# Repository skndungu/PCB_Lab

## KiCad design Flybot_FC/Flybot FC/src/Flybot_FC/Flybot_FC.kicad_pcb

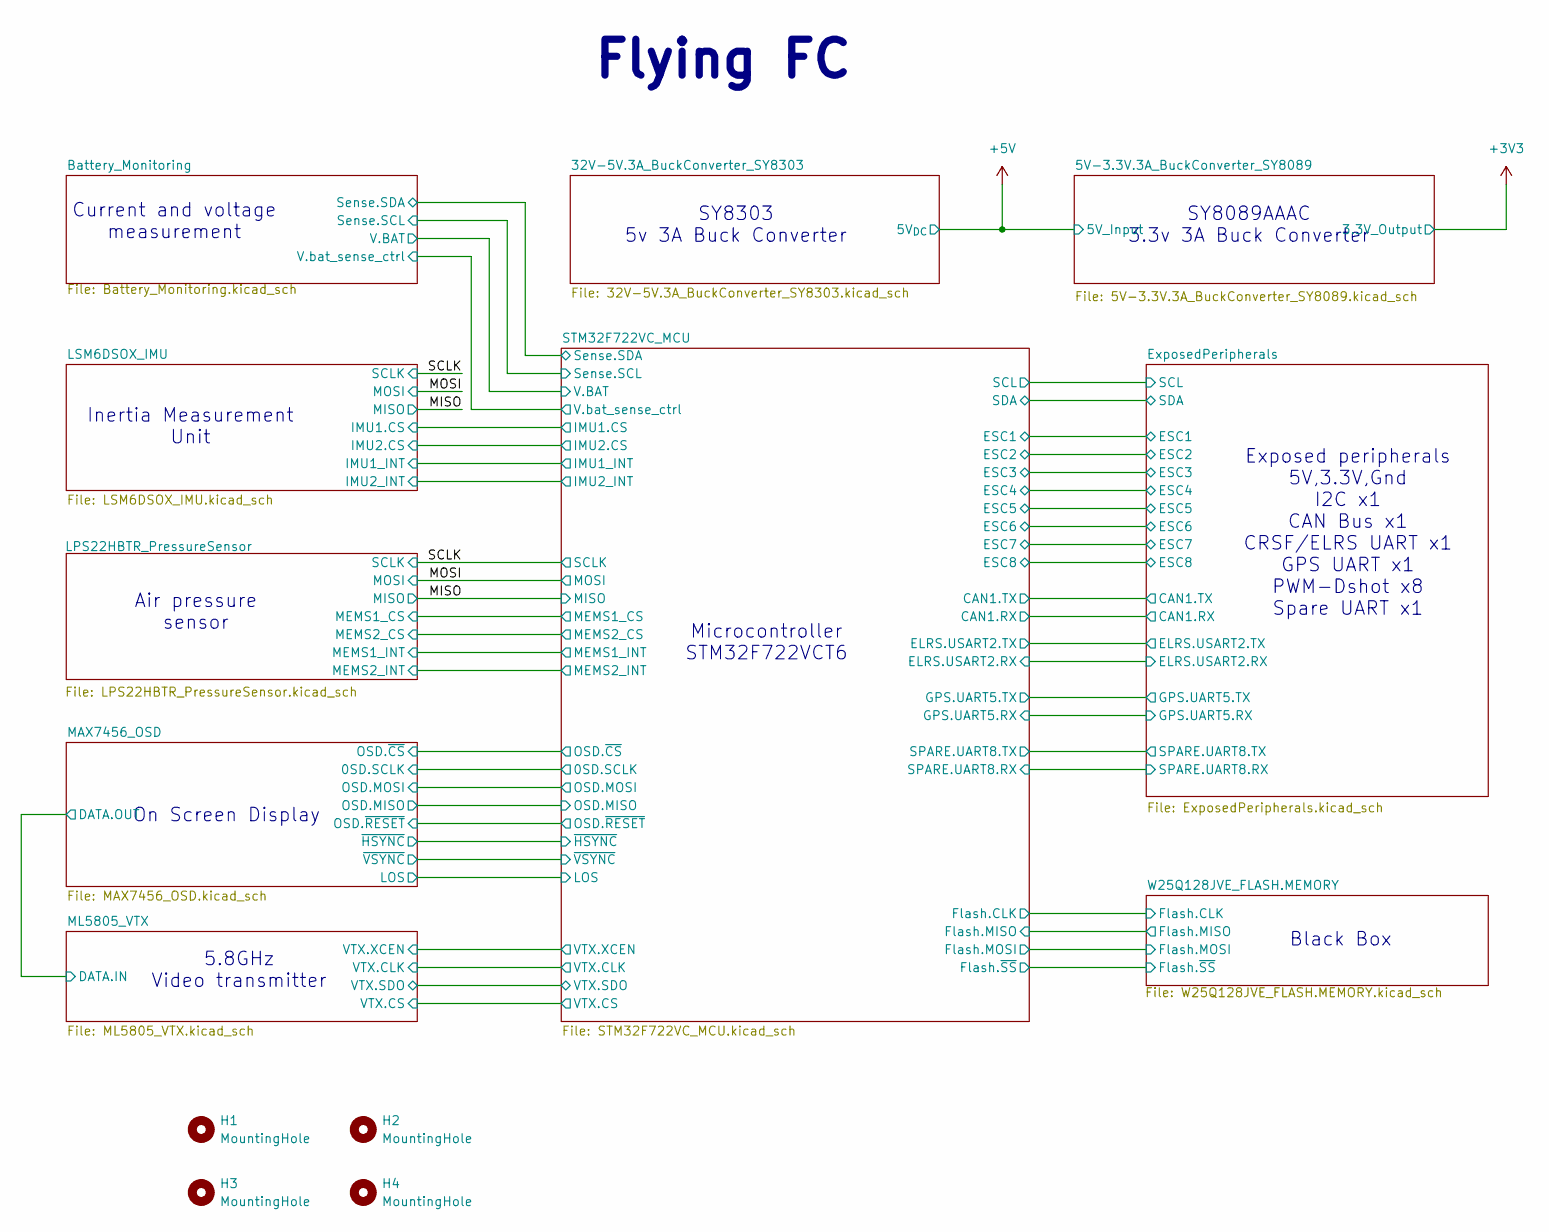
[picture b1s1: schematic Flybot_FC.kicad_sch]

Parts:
H1, H2, H3, H4: MountingHole; MountingHole_3mm

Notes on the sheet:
Inertia Measurement Unit
Microcontroller STM32F722VCT6
5.8GHz Video transmitter
Air pressure sensor
Flying FC
On Screen Display
SY8303 5v 3A Buck Converter
Exposed peripherals 5V,3.3V,Gnd I2C x1 CAN Bus x1 CRSF/ELRS UART x1 GPS UART x1 PWM-Dshot x8 Spare UART x1
SY8089AAAC 3.3v 3A Buck Converter
Black Box
Current and voltage measurement

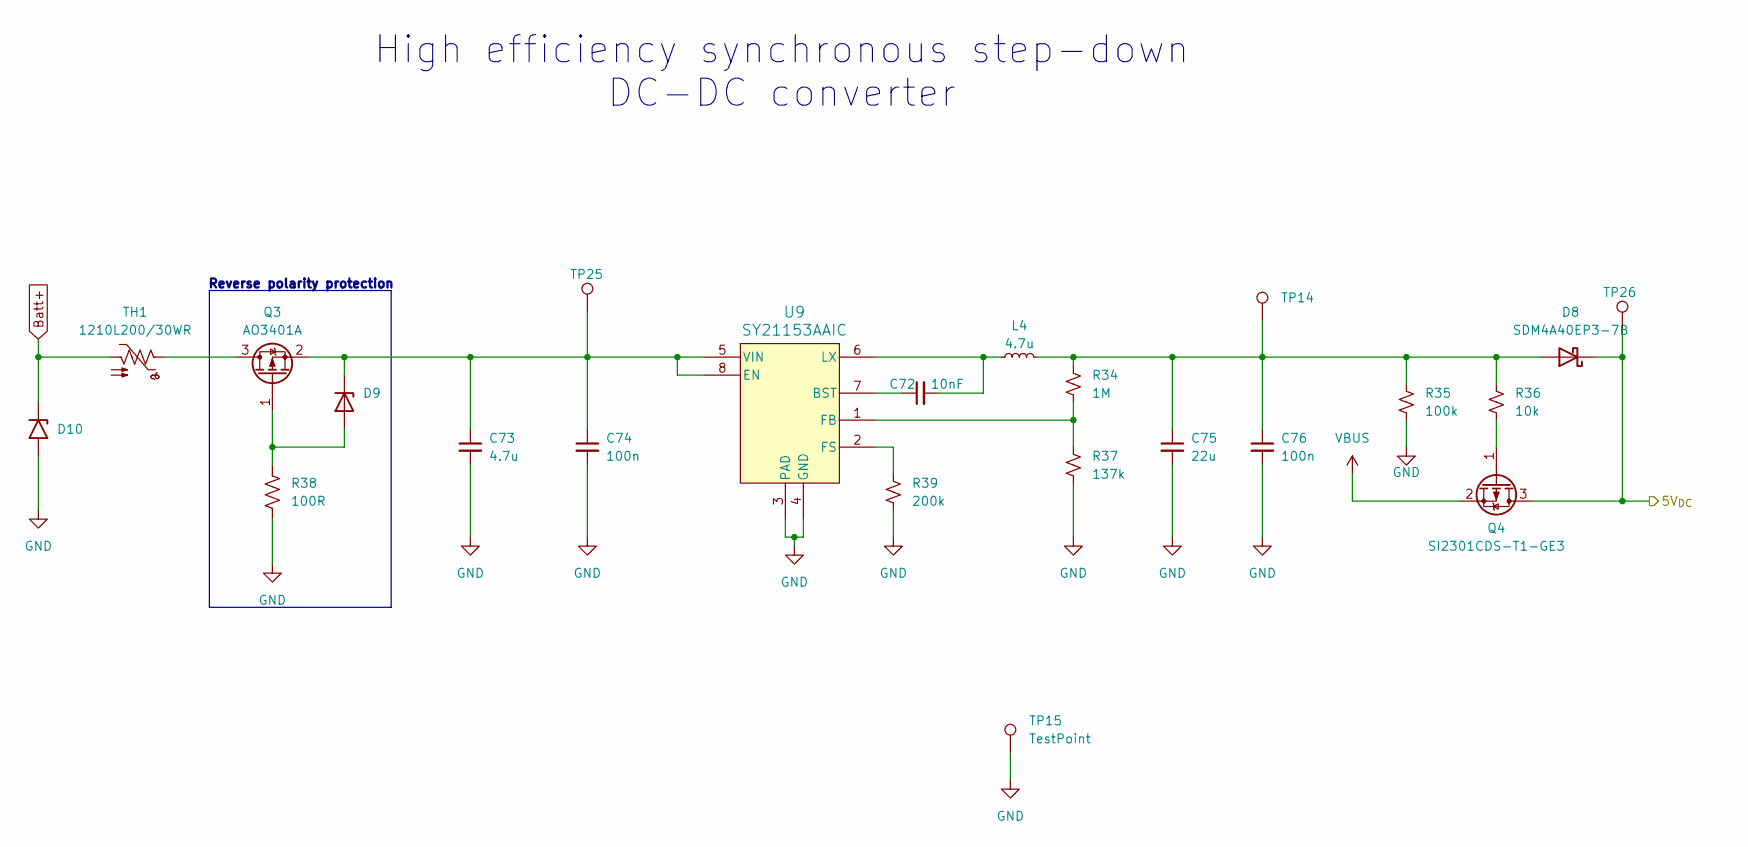
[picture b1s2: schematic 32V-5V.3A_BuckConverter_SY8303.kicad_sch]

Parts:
C72: 10nF; C_0402_1005Metric; JLC# C14663
C73: 4.7u; C_0603_1608Metric; JLC# C19702
C74: 100n; C_0402_1005Metric; JLC# C14663
C75: 22u; C_0402_1005Metric; JLC# C59461
C76: 100n; C_0402_1005Metric; JLC# C59461
D8: SDM4A40EP3-7B; D_0603_1608Metric
D9: BZX884B30L-G3-08; D_0402_1005Metric
D10: D15V0S1U2LP1610-7; D_0603_1608Metric
L4: 4.7u; L_1210_3225Metric; JLC# AFE322520S4R7MBT
Q3: AO3401A; SOT-23
Q4: SI2301CDS-T1-GE3; SOT-23
R34: 1M; R_0402_1005Metric; JLC# C23074
R35: 100k; R_0402_1005Metric; JLC# C25804
R36: 10k; R_0402_1005Metric; JLC# C25804
R37: 137k; R_0402_1005Metric; JLC# C25804
R38: 100R; R_0402_1005Metric
R39: 200k; R_0402_1005Metric; JLC# C2960716
TH1: 1210L200/30WR; Fuse_1206_3216Metric
TP14, TP15, TP25, TP26: TestPoint; TestPoint_Pad_D1.0mm
U9: SY21153AAIC; TSOT-23-8; JLC# C2071517

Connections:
+5V: D8.1 (K), Q4.3 (D), TP26.1; also elsewhere on the board
Batt+: D10.1 (A1), TH1.2; also elsewhere on the board
GND: C73.2, C74.2, C75.2, C76.2, D10.2 (A2), R35.2, R37.2, R38.2, R39.2, TP15.1, U9.3 (PAD), U9.4 (GND); also elsewhere on the board
unnamed: C75.1, C76.1, D8.2 (A), L4.2, R34.1, R35.1, R36.1, TP14.1
unnamed: D9.2 (A), Q3.1 (G), R38.1
unnamed: C73.1, C74.1, D9.1 (K), Q3.2 (S), TP25.1, U9.5 (VIN), U9.8 (EN)
unnamed: Q3.3 (D), TH1.1
unnamed: Q4.1 (G), R36.2
unnamed: C72.1, U9.7 (BST)
unnamed: R34.2, R37.1, U9.1 (FB)
unnamed: R39.1, U9.2 (FS)
unnamed: C72.2, L4.1, U9.6 (LX)
VBUS: Q4.2 (S); also elsewhere on the board

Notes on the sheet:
High efficiency synchronous step-down DC-DC converter
Reverse polarity protection

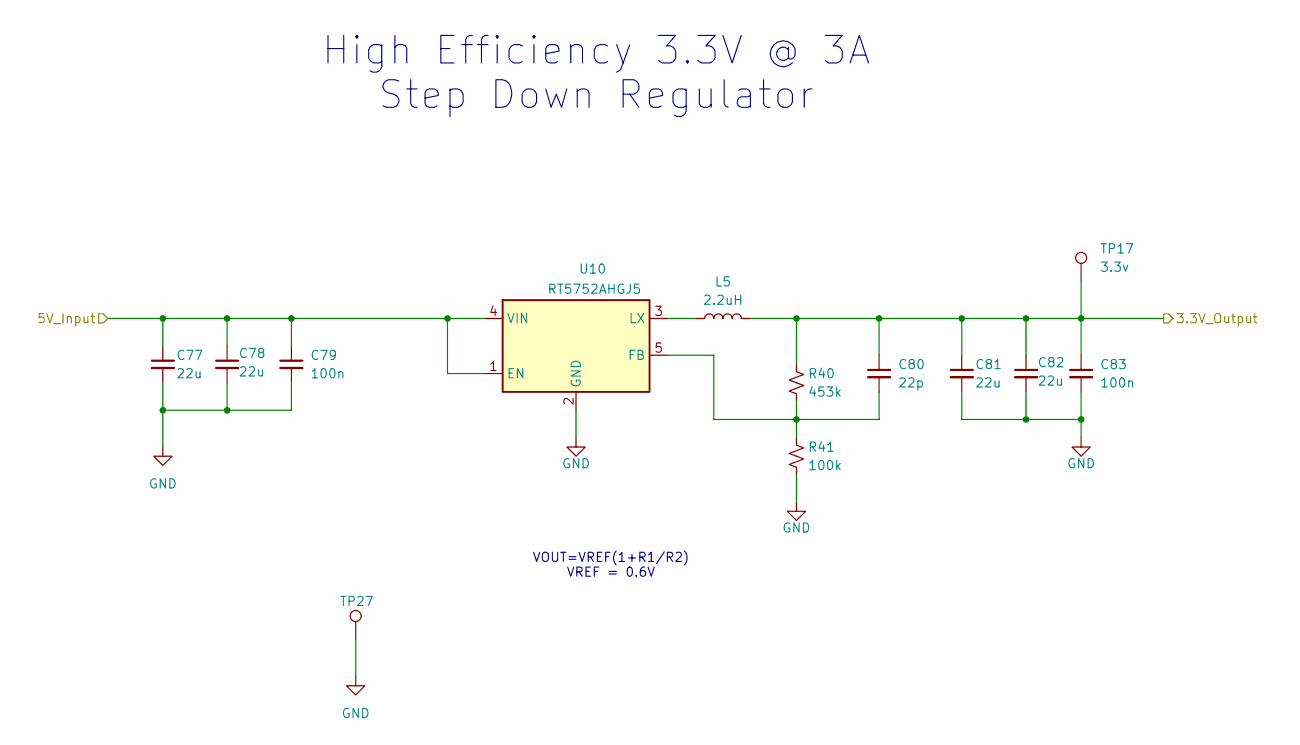
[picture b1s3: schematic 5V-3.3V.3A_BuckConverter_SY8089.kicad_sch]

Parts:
C77, C78, C81, C82: 22u; C_0402_1005Metric
C79, C83: 100n; C_0402_1005Metric
C80: 22p; C_0402_1005Metric
L5: 2.2uH; L_Murata_DFE201610P; MPN APH201610C2R2MP01
R40: 453k; R_0402_1005Metric
R41: 100k; R_0402_1005Metric
TP17: 3.3v; TestPoint_Pad_D1.0mm
TP27: TestPoint; TestPoint_Pad_D1.0mm
U10: RT5752AHGJ5; SOT-23-5

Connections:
+3V3: C80.1, C81.1, C82.1, C83.1, L5.2, R40.1, TP17.1; also elsewhere on the board
+5V: C77.1, C78.1, C79.1, U10.1 (EN), U10.4 (VIN); also elsewhere on the board
GND: C77.2, C78.2, C79.2, C81.2, C82.2, C83.2, R41.2, TP27.1, U10.2 (GND); also elsewhere on the board
unnamed: C80.2, R40.2, R41.1, U10.5 (FB)
unnamed: L5.1, U10.3 (LX)

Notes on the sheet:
VOUT=VREF(1+R1/R2) VREF = 0.6V
High Efficiency 3.3V @ 3A Step Down Regulator

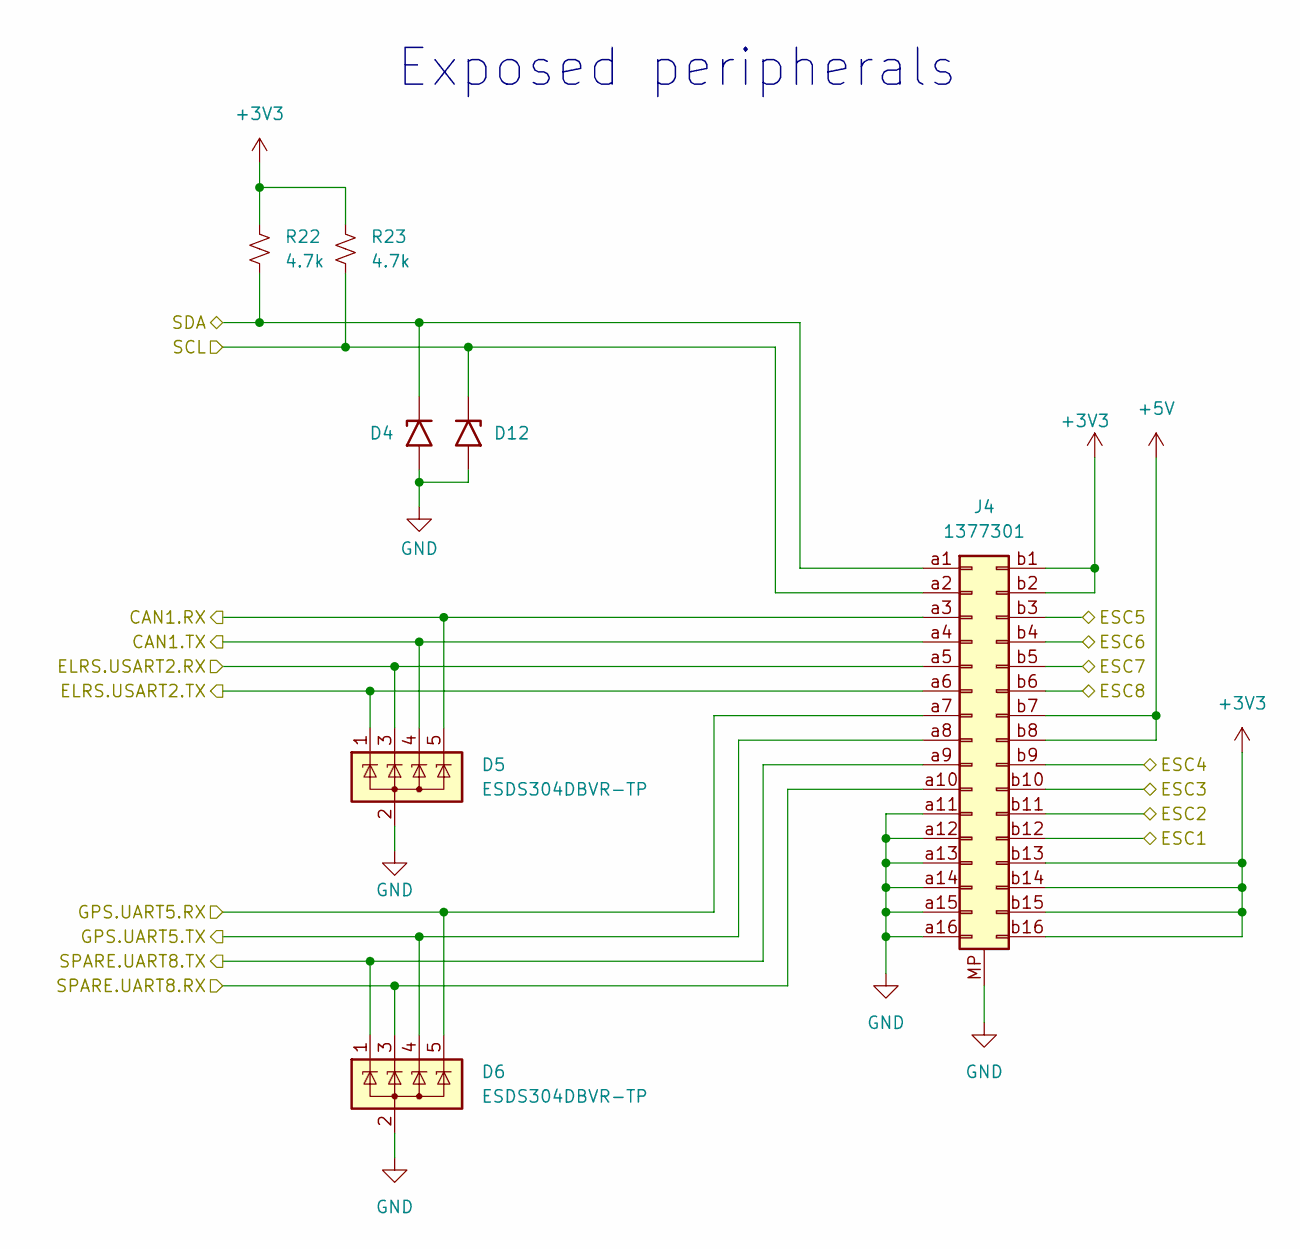
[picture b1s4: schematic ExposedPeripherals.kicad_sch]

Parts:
D4, D12: D1213A-01LP4-7B; D_0402_1005Metric
D5, D6: ESDS304DBVR-TP; SOT-23-5
J4: 1377301; PHOENIX_1377301
R22, R23: 4.7k; R_0402_1005Metric

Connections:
+3V3: J4.b1, J4.b2, J4.b13, J4.b14, J4.b15, J4.b16, R22.1, R23.1; also elsewhere on the board
+5V: J4.b7, J4.b8; also elsewhere on the board
/ExposedPeripherals/CAN1.RX: D5.5 (K), J4.a3; also elsewhere on the board
/ExposedPeripherals/CAN1.TX: D5.4 (K), J4.a4; also elsewhere on the board
/ExposedPeripherals/ELRS.USART2.RX: D5.3 (K), J4.a5; also elsewhere on the board
/ExposedPeripherals/ELRS.USART2.TX: D5.1 (K), J4.a6; also elsewhere on the board
/ExposedPeripherals/ESC1: J4.b12; also elsewhere on the board
/ExposedPeripherals/ESC2: J4.b11; also elsewhere on the board
/ExposedPeripherals/ESC3: J4.b10; also elsewhere on the board
/ExposedPeripherals/ESC4: J4.b9; also elsewhere on the board
/ExposedPeripherals/ESC5: J4.b3; also elsewhere on the board
/ExposedPeripherals/ESC6: J4.b4; also elsewhere on the board
/ExposedPeripherals/ESC7: J4.b5; also elsewhere on the board
/ExposedPeripherals/ESC8: J4.b6; also elsewhere on the board
/ExposedPeripherals/GPS.UART5.RX: D6.5 (K), J4.a7; also elsewhere on the board
/ExposedPeripherals/GPS.UART5.TX: D6.4 (K), J4.a8; also elsewhere on the board
/ExposedPeripherals/SCL: D12.1 (A1), J4.a2, R23.2; also elsewhere on the board
/ExposedPeripherals/SDA: D4.1 (A1), J4.a1, R22.2; also elsewhere on the board
/ExposedPeripherals/SPARE.UART8.RX: D6.3 (K), J4.a10; also elsewhere on the board
/ExposedPeripherals/SPARE.UART8.TX: D6.1 (K), J4.a9; also elsewhere on the board
GND: D4.2 (A2), D5.2 (A), D6.2 (A), D12.2 (A2), J4.MP, J4.a11, J4.a12, J4.a13, J4.a14, J4.a15, J4.a16; also elsewhere on the board

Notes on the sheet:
Exposed peripherals

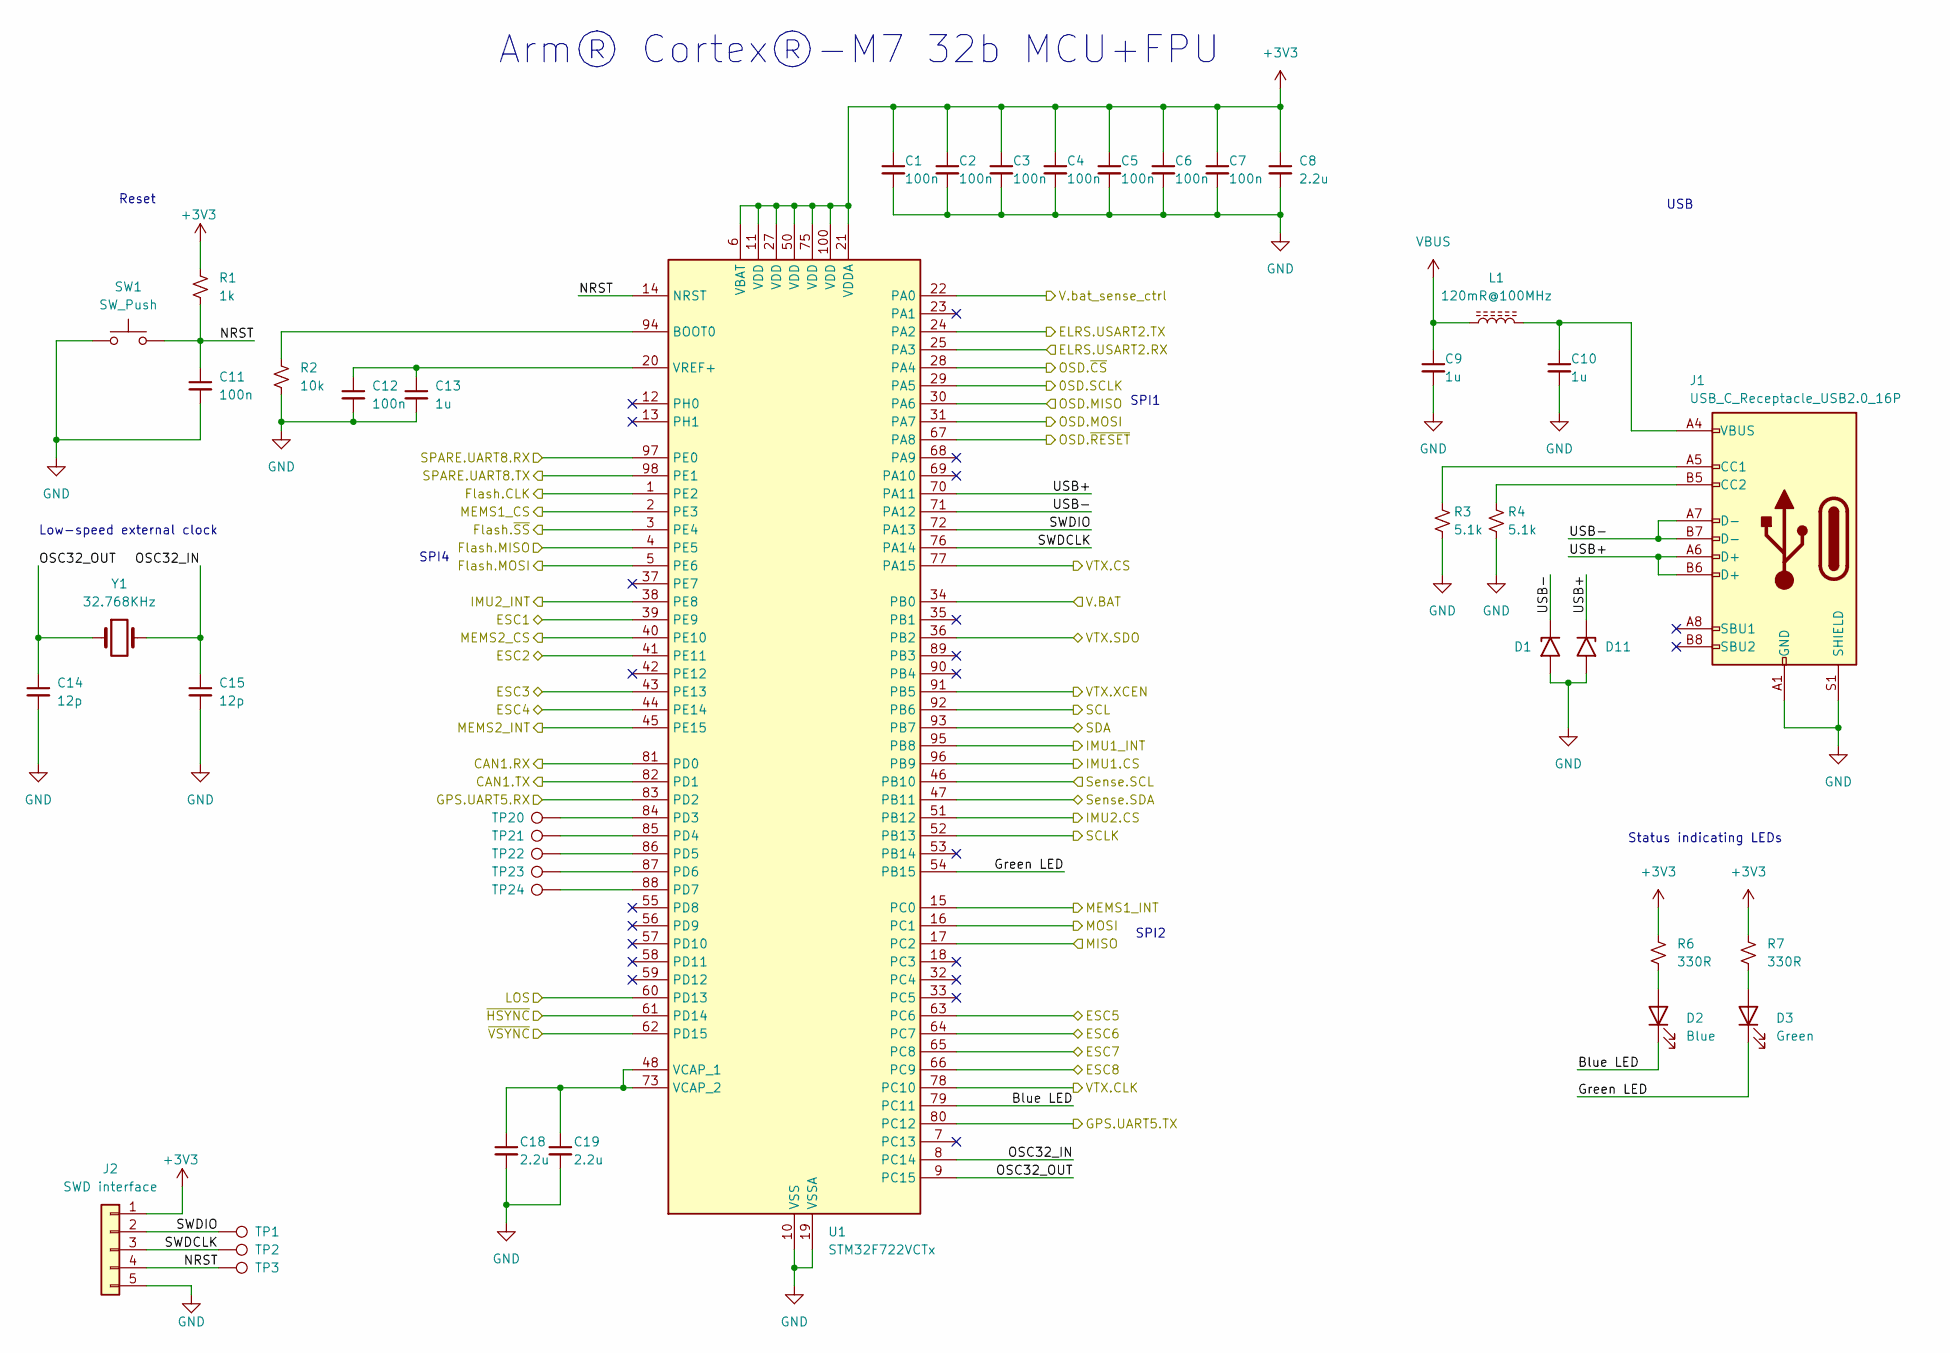
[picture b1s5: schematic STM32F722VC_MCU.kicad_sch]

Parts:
C1, C2, C3, C4, C5, C6, C7, C11, C12: 100n; C_0402_1005Metric
C8, C18, C19: 2.2u; C_0402_1005Metric
C9, C10, C13: 1u; C_0402_1005Metric
C14, C15: 12p; C_0402_1005Metric
D1, D11: D1213A-01LP4-7B; D_0402_1005Metric
D2: Blue; LED_0402_1005Metric
D3: Green; LED_0402_1005Metric
J1: USB_C_Receptacle_USB2.0_16P; GCT_USB4216-03-A_REVA
J2: SWD interface; PinHeader_1x05_P2.00mm_Vertical
L1: 120mR@100MHz; L_0402_1005Metric
R1: 1k; R_0402_1005Metric
R2: 10k; R_0402_1005Metric
R3, R4: 5.1k; R_0402_1005Metric
R6, R7: 330R; R_0402_1005Metric
SW1: SW_Push; SW_SKRPACE010
TP1, TP2, TP3, TP20, TP21, TP22, TP23, TP24: TestPoint; TestPoint_Pad_D1.0mm
U1: STM32F722VCTx; LQFP-100_14x14mm_P0.5mm
Y1: 32.768KHz; Crystal_SMD_3215-2Pin_3.2x1.5mm

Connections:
+3V3: C1.1, C2.1, C3.1, C4.1, C5.1, C6.1, C7.1, C8.1, J2.1, R1.1, R6.1, R7.1, U1.6 (VBAT), U1.11 (VDD), U1.21 (VDDA), U1.27 (VDD), U1.50 (VDD), U1.75 (VDD), U1.100 (VDD); also elsewhere on the board
/Battery_Monitoring/Sense.SCL: U1.46 (PB10); also elsewhere on the board
/Battery_Monitoring/Sense.SDA: U1.47 (PB11); also elsewhere on the board
/Battery_Monitoring/V.BAT: U1.34 (PB0); also elsewhere on the board
/Battery_Monitoring/V.bat_sense_ctrl: U1.22 (PA0); also elsewhere on the board
/ExposedPeripherals/CAN1.RX: U1.81 (PD0); also elsewhere on the board
/ExposedPeripherals/CAN1.TX: U1.82 (PD1); also elsewhere on the board
/ExposedPeripherals/ELRS.USART2.RX: U1.25 (PA3); also elsewhere on the board
/ExposedPeripherals/ELRS.USART2.TX: U1.24 (PA2); also elsewhere on the board
/ExposedPeripherals/ESC1: U1.39 (PE9); also elsewhere on the board
/ExposedPeripherals/ESC2: U1.41 (PE11); also elsewhere on the board
/ExposedPeripherals/ESC3: U1.43 (PE13); also elsewhere on the board
/ExposedPeripherals/ESC4: U1.44 (PE14); also elsewhere on the board
/ExposedPeripherals/ESC5: U1.63 (PC6); also elsewhere on the board
/ExposedPeripherals/ESC6: U1.64 (PC7); also elsewhere on the board
/ExposedPeripherals/ESC7: U1.65 (PC8); also elsewhere on the board
/ExposedPeripherals/ESC8: U1.66 (PC9); also elsewhere on the board
/ExposedPeripherals/GPS.UART5.RX: U1.83 (PD2); also elsewhere on the board
/ExposedPeripherals/GPS.UART5.TX: U1.80 (PC12); also elsewhere on the board
/ExposedPeripherals/SCL: U1.92 (PB6); also elsewhere on the board
/ExposedPeripherals/SDA: U1.93 (PB7); also elsewhere on the board
/ExposedPeripherals/SPARE.UART8.RX: U1.97 (PE0); also elsewhere on the board
/ExposedPeripherals/SPARE.UART8.TX: U1.98 (PE1); also elsewhere on the board
/LPS22HBTR_PressureSensor/MEMS1_CS: U1.2 (PE3); also elsewhere on the board
/LPS22HBTR_PressureSensor/MEMS1_INT: U1.15 (PC0); also elsewhere on the board
/LPS22HBTR_PressureSensor/MEMS2_CS: U1.40 (PE10); also elsewhere on the board
/LPS22HBTR_PressureSensor/MEMS2_INT: U1.45 (PE15); also elsewhere on the board
/LSM6DSOX_IMU/IMU1.CS: U1.96 (PB9); also elsewhere on the board
/LSM6DSOX_IMU/IMU1_INT: U1.95 (PB8); also elsewhere on the board
/LSM6DSOX_IMU/IMU2.CS: U1.51 (PB12); also elsewhere on the board
/LSM6DSOX_IMU/IMU2_INT: U1.38 (PE8); also elsewhere on the board
/MAX7456_OSD/0SD.SCLK: U1.29 (PA5); also elsewhere on the board
/MAX7456_OSD/LOS: U1.60 (PD13); also elsewhere on the board
/MAX7456_OSD/OSD.MISO: U1.30 (PA6); also elsewhere on the board
/MAX7456_OSD/OSD.MOSI: U1.31 (PA7); also elsewhere on the board
/MAX7456_OSD/OSD.~CS: U1.28 (PA4); also elsewhere on the board
/MAX7456_OSD/OSD.~RESET: U1.67 (PA8); also elsewhere on the board
/MAX7456_OSD/~HSYNC: U1.61 (PD14); also elsewhere on the board
/MAX7456_OSD/~VSYNC: U1.62 (PD15); also elsewhere on the board
/MISO: U1.17 (PC2); also elsewhere on the board
/ML5805_VTX/VTX.CLK: U1.78 (PC10); also elsewhere on the board
/ML5805_VTX/VTX.CS: U1.77 (PA15); also elsewhere on the board
/ML5805_VTX/VTX.SDO: U1.36 (PB2); also elsewhere on the board
/ML5805_VTX/VTX.XCEN: U1.91 (PB5); also elsewhere on the board
/MOSI: U1.16 (PC1); also elsewhere on the board
/SCLK: U1.52 (PB13); also elsewhere on the board
/STM32F722VC_MCU/Blue LED: D2.1 (K), U1.79 (PC11)
/STM32F722VC_MCU/Flash.CLK: U1.1 (PE2); also elsewhere on the board
/STM32F722VC_MCU/Flash.MISO: U1.4 (PE5); also elsewhere on the board
/STM32F722VC_MCU/Flash.MOSI: U1.5 (PE6); also elsewhere on the board
/STM32F722VC_MCU/Flash.~SS: U1.3 (PE4); also elsewhere on the board
/STM32F722VC_MCU/Green LED: D3.1 (K), U1.54 (PB15)
/STM32F722VC_MCU/NRST: C11.1, J2.4, R1.2, SW1.2, TP3.1, U1.14 (NRST)
/STM32F722VC_MCU/OSC32_IN: C15.1, U1.8 (PC14), Y1.2
/STM32F722VC_MCU/OSC32_OUT: C14.1, U1.9 (PC15), Y1.1
/STM32F722VC_MCU/SWDCLK: J2.3, TP2.1, U1.76 (PA14)
/STM32F722VC_MCU/SWDIO: J2.2, TP1.1, U1.72 (PA13)
/STM32F722VC_MCU/USB+: D11.1 (A1), J1.A6 (D+), J1.B6 (D+), U1.70 (PA11)
/STM32F722VC_MCU/USB-: D1.1 (A1), J1.A7 (D-), J1.B7 (D-), U1.71 (PA12)
GND: C1.2, C2.2, C3.2, C4.2, C5.2, C6.2, C7.2, C8.2, C9.2, C10.2, C11.2, C12.2, C13.2, C14.2, C15.2, C18.2, C19.2, D1.2 (A2), D11.2 (A2), J1.A1 (GND), J1.B1 (GND), J1.S1 (SHIELD), J2.5, R2.2, R3.2, R4.2, SW1.1, U1.10 (VSS), U1.19 (VSSA), U1.26 (VSS), U1.49 (VSS), U1.74 (VSS), U1.99 (VSS); also elsewhere on the board
unnamed: C10.1, J1.A4 (VBUS), J1.B4 (VBUS), L1.2
unnamed: D2.2 (A), R6.2
unnamed: D3.2 (A), R7.2
unnamed: J1.A5 (CC1), R3.1
unnamed: J1.B5 (CC2), R4.1
unnamed: R2.1, U1.94 (BOOT0)
unnamed: TP20.1, U1.84 (PD3)
unnamed: TP21.1, U1.85 (PD4)
unnamed: TP22.1, U1.86 (PD5)
unnamed: TP23.1, U1.87 (PD6)
unnamed: TP24.1, U1.88 (PD7)
unnamed: C18.1, C19.1, U1.48 (VCAP_1), U1.73 (VCAP_2)
unnamed: C12.1, C13.1, U1.20 (VREF+)
VBUS: C9.1, L1.1; also elsewhere on the board

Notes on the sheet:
Arm® Cortex®-M7 32b MCU+FPU
SPI2
Status indicating LEDs
SPI1
USB
Low-speed external clock
SPI4
Reset

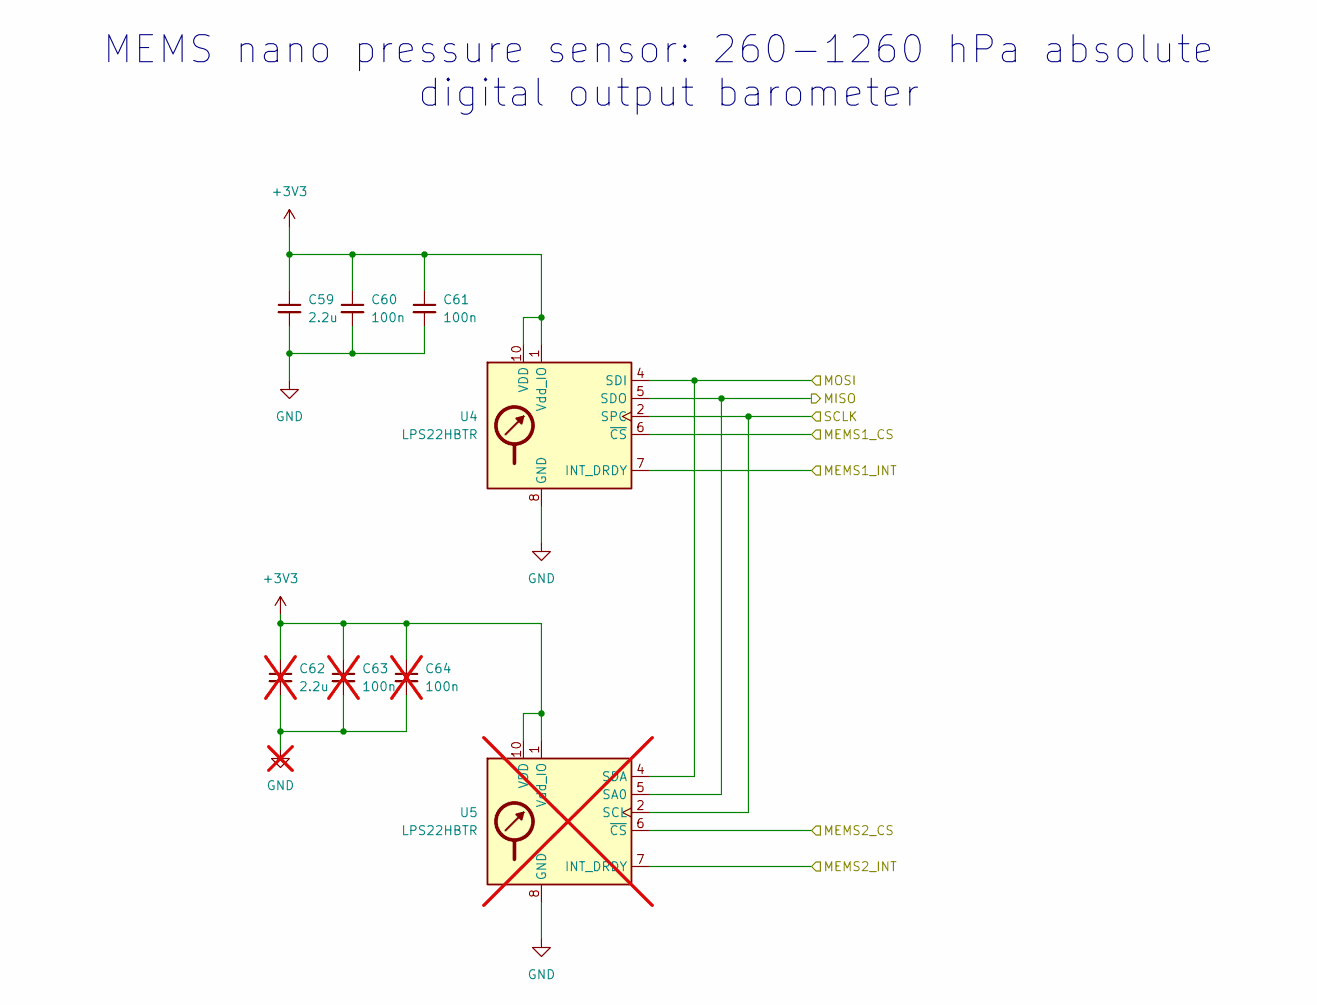
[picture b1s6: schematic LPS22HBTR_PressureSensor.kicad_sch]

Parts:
C59: 2.2u; C_0402_1005Metric
C60, C61: 100n; C_0402_1005Metric
C62: 2.2u; C_0402_1005Metric; not fitted
C63, C64: 100n; C_0402_1005Metric; not fitted
U4: LPS22HBTR; ST_HLGA-10_2x2mm_P0.5mm_LayoutBorder3x2y
U5: LPS22HBTR; ST_HLGA-10_2x2mm_P0.5mm_LayoutBorder3x2y; not fitted

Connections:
+3V3: C59.1, C60.1, C61.1, C62.1, C63.1, C64.1, U4.1 (Vdd_IO), U4.10 (VDD), U5.1 (Vdd_IO), U5.10 (VDD); also elsewhere on the board
/LPS22HBTR_PressureSensor/MEMS1_CS: U4.6 (~CS); also elsewhere on the board
/LPS22HBTR_PressureSensor/MEMS1_INT: U4.7 (INT_DRDY); also elsewhere on the board
/LPS22HBTR_PressureSensor/MEMS2_CS: U5.6 (~CS); also elsewhere on the board
/LPS22HBTR_PressureSensor/MEMS2_INT: U5.7 (INT_DRDY); also elsewhere on the board
/MISO: U4.5 (SDO), U5.5 (SA0); also elsewhere on the board
/MOSI: U4.4 (SDI), U5.4 (SDA); also elsewhere on the board
/SCLK: U4.2 (SPC), U5.2 (SCL); also elsewhere on the board
GND: C59.2, C60.2, C61.2, C62.2, C63.2, C64.2, U4.3 (GND), U4.8 (GND), U4.9 (GND), U5.3 (GND), U5.8 (GND), U5.9 (GND); also elsewhere on the board

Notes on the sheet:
MEMS nano pressure sensor: 260-1260 hPa absolute digital output barometer

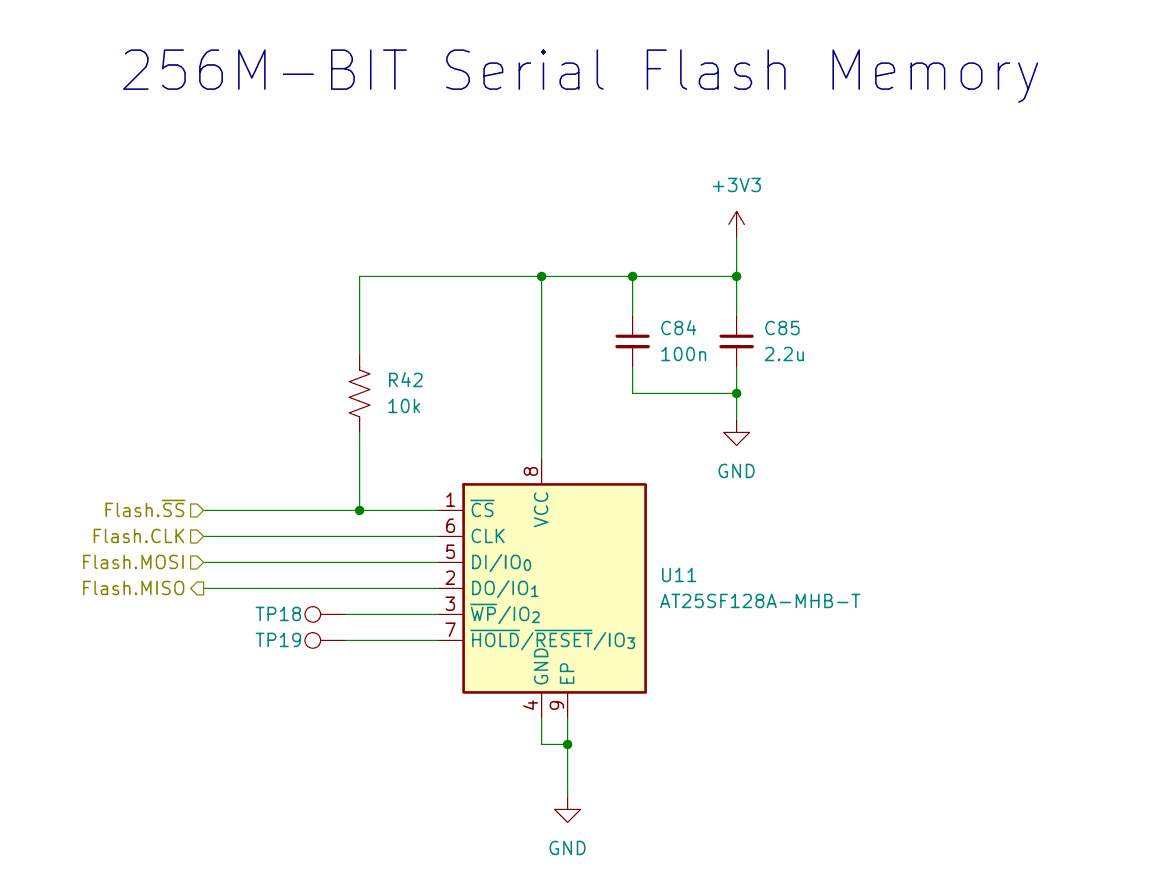
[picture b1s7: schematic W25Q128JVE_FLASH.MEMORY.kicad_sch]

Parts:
C84: 100n; C_0402_1005Metric
C85: 2.2u; C_0402_1005Metric
R42: 10k; R_0402_1005Metric
TP18, TP19: TestPoint; TestPoint_Pad_D1.0mm
U11: AT25SF128A-MHB-T; DFN-8-1EP_6x5mm_P1.27mm_EP4x4mm

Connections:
+3V3: C84.1, C85.1, R42.1, U11.8 (VCC); also elsewhere on the board
/STM32F722VC_MCU/Flash.CLK: U11.6 (CLK); also elsewhere on the board
/STM32F722VC_MCU/Flash.MISO: U11.2 (DO/IO_{1}); also elsewhere on the board
/STM32F722VC_MCU/Flash.MOSI: U11.5 (DI/IO_{0}); also elsewhere on the board
/STM32F722VC_MCU/Flash.~SS: R42.2, U11.1 (~CS); also elsewhere on the board
GND: C84.2, C85.2, U11.4 (GND), U11.9 (EP); also elsewhere on the board
unnamed: TP19.1, U11.7 (~HOLD/~RESET/IO_{3})
unnamed: TP18.1, U11.3 (~WP/IO_{2})

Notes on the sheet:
256M-BIT Serial Flash Memory

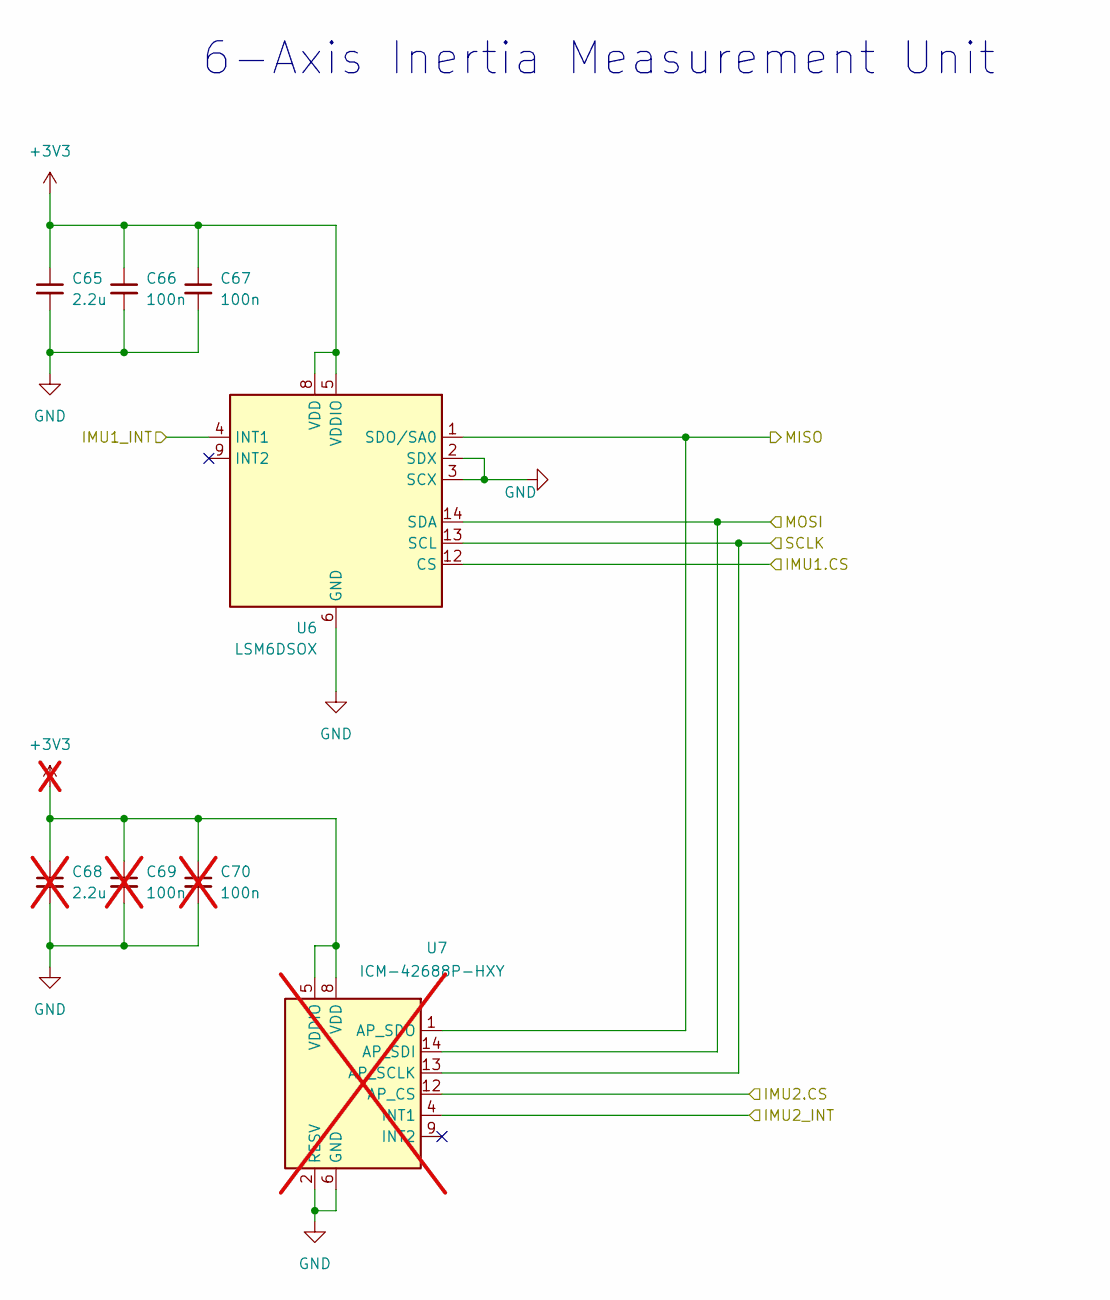
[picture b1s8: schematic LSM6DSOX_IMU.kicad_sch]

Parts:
C65: 2.2u; C_0402_1005Metric
C66, C67: 100n; C_0402_1005Metric
C68: 2.2u; C_0402_1005Metric; not fitted
C69, C70: 100n; C_0402_1005Metric; not fitted
U6: LSM6DSOX; LGA-14_3x2.5mm_P0.5mm_LayoutBorder3x4y
U7: ICM-42688P-HXY; LGA-14_3x2.5mm_P0.5mm_LayoutBorder3x4y; not fitted

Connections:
+3V3: C65.1, C66.1, C67.1, C68.1, C69.1, C70.1, U6.5 (VDDIO), U6.8 (VDD), U7.5 (VDDIO), U7.8 (VDD); also elsewhere on the board
/LSM6DSOX_IMU/IMU1.CS: U6.12 (CS); also elsewhere on the board
/LSM6DSOX_IMU/IMU1_INT: U6.4 (INT1); also elsewhere on the board
/LSM6DSOX_IMU/IMU2.CS: U7.12 (AP_CS); also elsewhere on the board
/LSM6DSOX_IMU/IMU2_INT: U7.4 (INT1); also elsewhere on the board
/MISO: U6.1 (SDO/SA0), U7.1 (AP_SDO); also elsewhere on the board
/MOSI: U6.14 (SDA), U7.14 (AP_SDI); also elsewhere on the board
/SCLK: U6.13 (SCL), U7.13 (AP_SCLK); also elsewhere on the board
GND: C65.2, C66.2, C67.2, C68.2, C69.2, C70.2, U6.2 (SDX), U6.3 (SCX), U6.6 (GND), U6.7 (GND), U7.2 (RESV), U7.3 (RESV), U7.6 (GND), U7.7 (RESV), U7.10 (RESV), U7.11 (RESV); also elsewhere on the board

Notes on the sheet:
6-Axis Inertia Measurement Unit

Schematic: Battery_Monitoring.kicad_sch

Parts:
C71: 100n; C_0402_1005Metric
D7: Red; LED_0402_1005Metric
J5: Conn_01x02; CONN_SM02B-SFHLS-TF
Q1: CMLDM7484 TR PBFREE; SOT-563
R24, R31, R33: 10K; R_0402_1005Metric
R25, R26: 4.7k; R_0402_1005Metric
R27, R28: 1K; R_0402_1005Metric
R29: 2mR; R_0603_1608Metric
R30: 76.8k; R_0402_1005Metric
R32: 330R; R_0402_1005Metric
TP13: TestPoint; TestPoint_Pad_D1.0mm
U8: INA219AIDCNR; SOT-23-8

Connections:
+3V3: C71.1, R25.1, R26.1, U8.4 (VS); also elsewhere on the board
/Battery_Monitoring/Sense.SCL: R26.2, U8.5 (SCL); also elsewhere on the board
/Battery_Monitoring/Sense.SDA: R25.2, U8.6 (SDA); also elsewhere on the board
/Battery_Monitoring/V.BAT: R30.2, R33.1; also elsewhere on the board
/Battery_Monitoring/V.bat_sense_ctrl: R28.2; also elsewhere on the board
Batt+: Q1.3 (D), R24.1, R29.2, TP13.1, U8.2 (IN-); also elsewhere on the board
GND: C71.2, D7.1 (K), J5.2, J5.MP (MountPin), Q1.1 (S), R31.2, R33.2, U8.3 (GND), U8.7 (A0), U8.8 (A1); also elsewhere on the board
unnamed: D7.2 (A), R32.2
unnamed: J5.1, R29.1, R32.1, U8.1 (IN+)
unnamed: Q1.6 (D), R27.2
unnamed: Q1.2 (G), R28.1, R31.1
unnamed: Q1.5 (G), R24.2, R27.1
unnamed: Q1.4 (S), R30.1

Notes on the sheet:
Current sensing
Battery voltage monitoring
I2C Address: 0x40

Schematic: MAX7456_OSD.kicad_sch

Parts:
C20: 2.2u; C_0402_1005Metric
C21, C22, C23, C26: 100n; C_0402_1005Metric
C24, C25: 47u; SMD 3216-16
J3: Camera; SM03B-SRSS-TB(LF)(SN); MPN SM03B-SRSS-TB
R8, R9, R10, R11: 1k; R_0402_1005Metric
R12, R13: 75R; R_0402_1005Metric
TP4, TP5: TestPoint; TestPoint_Pad_D1.0mm
U2: MAX7456EUI+
Y3: 27MHz; Crystal_SMD_2016-4Pin_2.0x1.6mm; MPN SX1B27.000F0810F30

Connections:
+5V: C20.1, C21.1, C22.1, C23.1, J3.1, R8.1, R9.1, R10.1, R11.1, U2.3 (DVDD), U2.21 (AVDD), U2.24 (PVDD); also elsewhere on the board
/MAX7456_OSD/0SD.SCLK: U2.10 (SCLK); also elsewhere on the board
/MAX7456_OSD/DATA.OUT: R12.2, TP4.1; also elsewhere on the board
/MAX7456_OSD/LOS: R10.2, U2.12 (LOS); also elsewhere on the board
/MAX7456_OSD/OSD.MISO: U2.11 (SDOUT); also elsewhere on the board
/MAX7456_OSD/OSD.MOSI: U2.9 (SDIN); also elsewhere on the board
/MAX7456_OSD/OSD.~CS: U2.8 (~CS); also elsewhere on the board
/MAX7456_OSD/OSD.~RESET: R11.2, U2.19 (~RESET); also elsewhere on the board
/MAX7456_OSD/VIN: C26.1, J3.2, R13.1
/MAX7456_OSD/~HSYNC: R8.2, U2.18 (~HSYNC); also elsewhere on the board
/MAX7456_OSD/~VSYNC: R9.2, U2.17 (~VSYNC); also elsewhere on the board
GND: C20.2, C21.2, C22.2, C23.2, J3.3, J3.MP (MountPin), R13.2, U2.4 (DGND), U2.20 (AGND), U2.23 (PGND), U2.29 (EP), Y3.2, Y3.4; also elsewhere on the board
unnamed: C24.2, C25.2, R12.1
unnamed: U2.5 (CLKIN), Y3.3
unnamed: TP5.1, U2.7 (CLKOUT)
unnamed: C25.1, U2.25 (SAG)
unnamed: C26.2, U2.22 (VIN)
unnamed: C24.1, U2.26 (VOUT)
unnamed: U2.6 (XFB), Y3.1

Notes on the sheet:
Single-Channel Monochrome On-Screen Display with Integrated EEPROM
